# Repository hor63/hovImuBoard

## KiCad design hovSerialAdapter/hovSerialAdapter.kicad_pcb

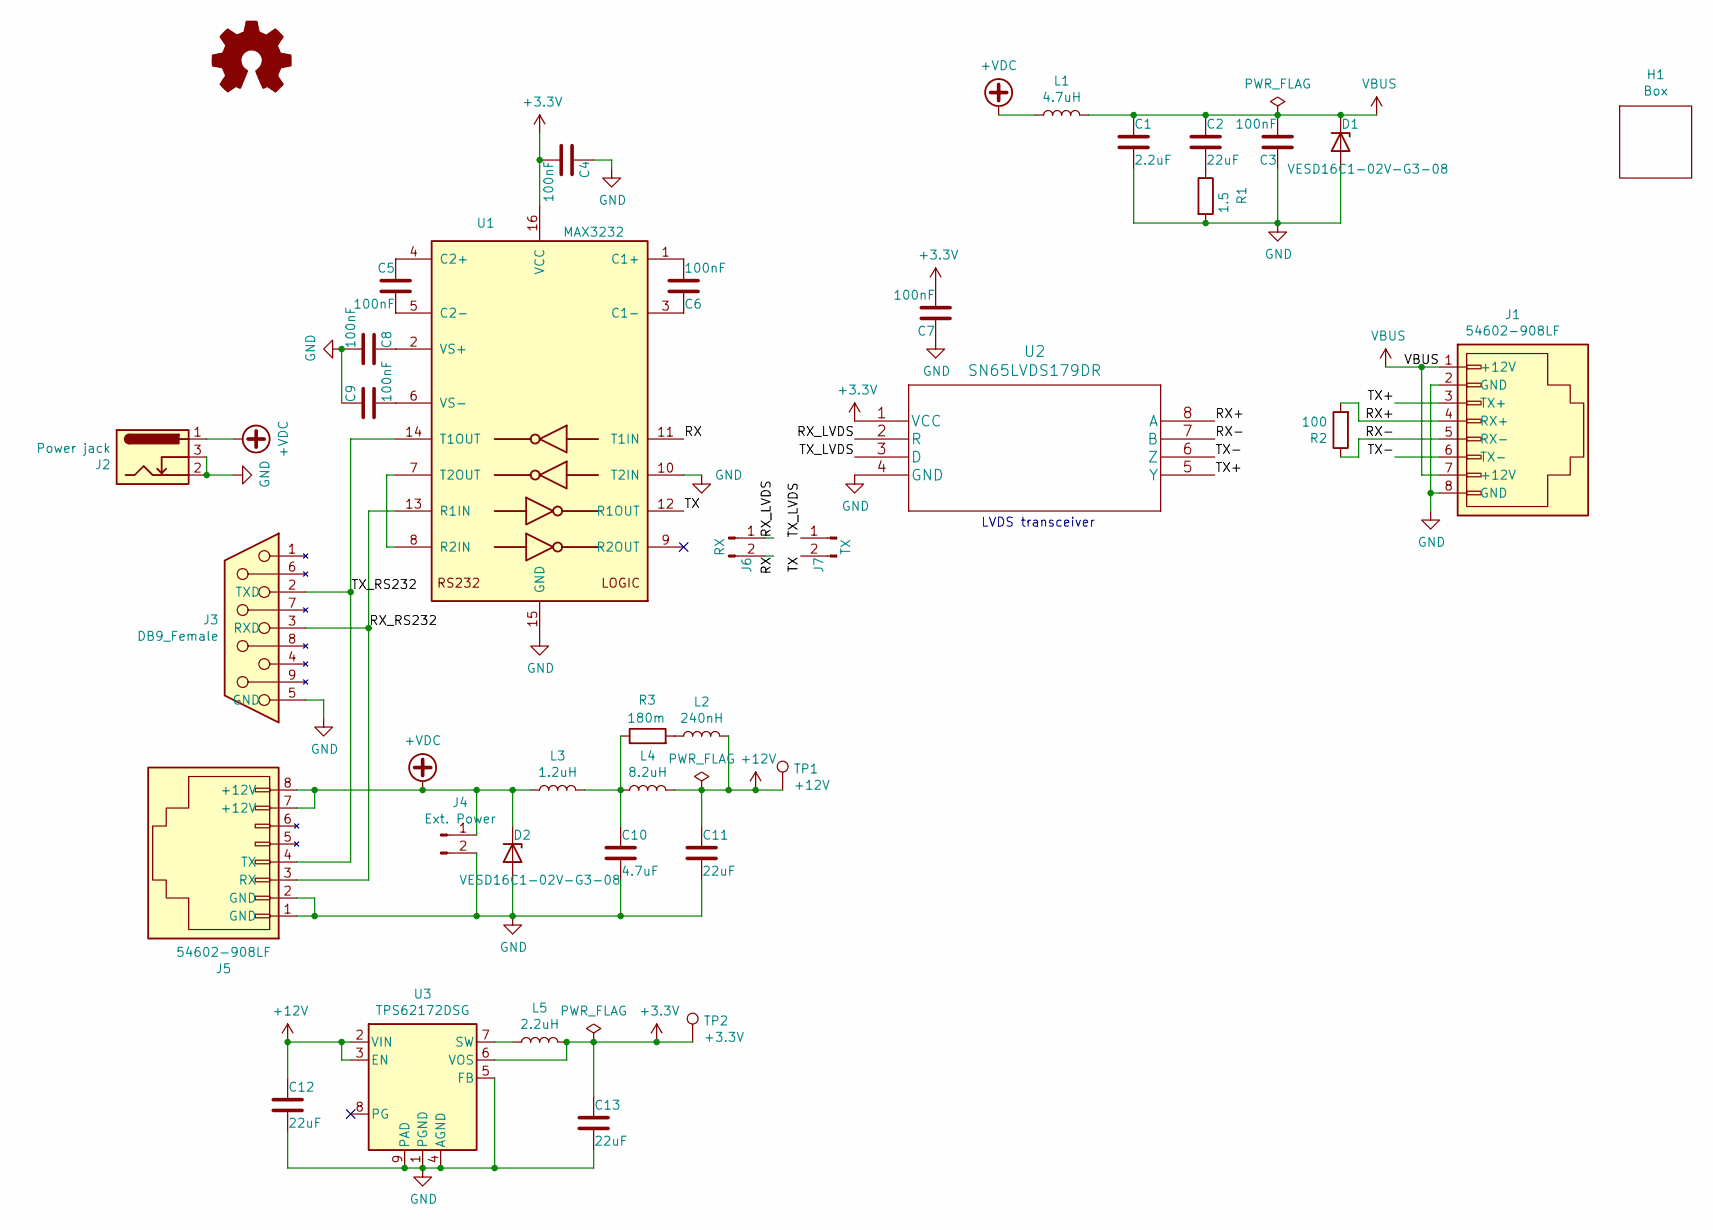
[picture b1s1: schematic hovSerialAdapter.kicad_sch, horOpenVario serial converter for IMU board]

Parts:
C1: 2.2uF; C_0805_2012Metric; MPN CL21B225KAFNNNE; Digi-Key_PN 1276-2954-1-ND
C2, C11, C12, C13: 22uF; C_1210_3225Metric; MPN CL32B226KAJNNNE; Digi-Key_PN 1276-3392-1-ND
C3, C4, C5, C6, C7, C8, C9: 100nF; C_0603_1608Metric; MPN CC0603KRX7R8BB104; Digi-Key_PN 311-1341-1-ND
C10: 4.7uF; C_1206_3216Metric; MPN C1206C475K3RACTU; Digi-Key_PN 399-8204-1-ND
D1, D2: VESD16C1-02V-G3-08; D_SOD-523; MPN VESD16C1-02V-G3-08; Digi-Key_PN VESD16C1-02V-G3-08GICT-ND
H1: Box; Box-MB655030; MPN MB655030; Digi-Key_PN HM5530-ND
J1, J5: 54602-908LF; Ethernet_Jack_54602-908LF; MPN 54602-908LF; Digi-Key_PN 609-1046-ND
J2: Power jack; CUI_PJ-036AH-SMT-TR; MPN PJ-036AH-SMT-TR; Digi-Key_PN CP-036AHPJCT-ND
J3: DB9_Female; DSUB-9_Female_EdgeMount_P2.77mm; MPN L77SDE09S; Digi-Key_PN L77SDE09S-ND
J4: Ext. Power; PinHeader_1x02_P2.54mm_Vertical
J6: RX; PinHeader_1x02_P2.54mm_Vertical
J7: TX; PinHeader_1x02_P2.54mm_Vertical
L1: 4.7uH; L_1812_4532Metric; MPN LQH43PN4R7M26L; Digi-Key_PN 490-13388-1-ND
L2: 240nH; L_0805_2012Metric; MPN LQM21PNR24MEHD; Digi-Key_PN 490-15988-1-ND
L3: 1.2uH; IND_1231AS-H-1R2N=P3; MPN 1231AS-H-1R2N=P3; Digi-Key_PN 490-14180-1-ND
L4: 8.2uH; IND_LQH43PH8R2M26L; MPN LQH43PH8R2M26L; Digi-Key_PN 490-16115-1-ND
L5: 2.2uH; IND_LQH3NPN2R2MMEL; MPN LQH3NPN2R2MMEL; Digi-Key_PN 490-15950-1-ND
LOGO1: Logo_Open_Hardware_Small; OSHW-Symbol_6.7x6mm_SilkScreen
R1: 1.5; R_0805_2012Metric; MPN ERJ-6DQF1R5V; Digi-Key_PN P19272CT-ND
R2: 100; R_0603_1608Metric; MPN ERJ-PA3F1000V; Digi-Key_PN P100BYCT-ND
R3: 180m; R_0805_2012Metric; MPN ERJ-6DSFR18V; Digi-Key_PN P19314CT-ND
TP1: +12V; TestPoint_THTPad_D1.0mm_Drill0.5mm
TP2: +3.3V; TestPoint_THTPad_D1.0mm_Drill0.5mm
U1: MAX3232; TSSOP-16_4.4x5mm_P0.65mm; MPN MAX3232IPWR; Digi-Key_PN 296-13100-1-ND
U2: SN65LVDS179DR; SOIC-8_3.9x4.9mm_P1.27mm; MPN SN65LVDS179DR; Digi-Key_PN 296-46329-1-ND
U3: TPS62172DSG; WSON-8-1EP_2x2mm_P0.5mm_EP0.9x1.6mm_ThermalVias; MPN TPS62172DSGR; Digi-Key_PN 296-39449-1-ND

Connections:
+3V3: C4.1, C7.1, C13.2, L5.2, TP2.1, U1.16 (VCC), U2.1 (VCC), U3.6 (VOS)
+12V: C11.2, C12.2, L2.2, L4.2, TP1.1, U3.2 (VIN), U3.3 (EN)
+VDC: D2.1 (K), J2.1, J4.1, J5.7 (+12V), J5.8 (+12V), L1.1, L3.1
/RX: J6.2, U1.11 (T1IN)
/RX+: J1.4 (RX+), R2.2, U2.8 (A)
/RX-: J1.5 (RX-), R2.1, U2.7 (B)
/RX_LVDS: J6.1, U2.2 (R)
/RX_RS232: J3.3 (RXD), J5.3 (RX), U1.13 (R1IN)
/TX: J7.2, U1.12 (R1OUT)
/TX+: J1.3 (TX+), U2.5 (Y)
/TX-: J1.6 (TX-), U2.6 (Z)
/TX_LVDS: J7.1, U2.3 (D)
/TX_RS232: J3.2 (TXD), J5.4 (TX), U1.14 (T1OUT)
GND: C1.1, C3.2, C4.2, C7.2, C8.1, C9.2, C10.1, C11.1, C12.1, C13.1, D1.2 (A), D2.2 (A), J1.2 (GND), J1.8 (GND), J2.2, J2.3, J3.5 (GND), J4.2, J5.1 (GND), J5.2 (GND), R1.2, U1.10 (T2IN), U1.15 (GND), U2.4 (GND), U3.1 (PGND), U3.4 (AGND), U3.5 (FB), U3.9 (PAD)
unnamed: C2.1, R1.1
unnamed: C5.1, U1.5 (C2-)
unnamed: C5.2, U1.4 (C2+)
unnamed: C6.1, U1.1 (C1+)
unnamed: C6.2, U1.3 (C1-)
unnamed: C8.2, U1.2 (VS+)
unnamed: C9.1, U1.6 (VS-)
unnamed: C10.2, L3.2, L4.1, R3.1
unnamed: L2.1, R3.2
unnamed: L5.1, U3.7 (SW)
unnamed: U1.7 (T2OUT), U1.8 (R2IN)
VBUS: C1.2, C2.2, C3.1, D1.1 (K), J1.1 (+12V), J1.7 (+12V), L1.2

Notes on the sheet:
LVDS transceiver

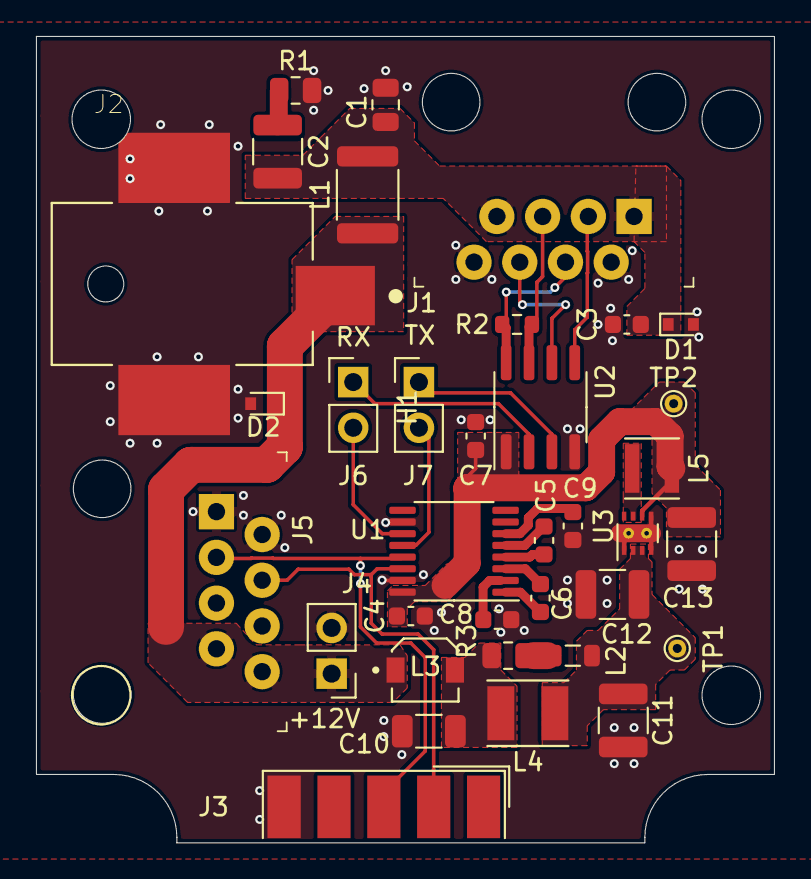
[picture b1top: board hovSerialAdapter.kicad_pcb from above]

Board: 2 copper layers, 41.0 x 44.8 mm, 37 parts (1 on the bottom side), 26 nets.

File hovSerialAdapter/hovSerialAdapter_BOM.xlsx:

Reference | Value | Description | Digi-Key_PN | MPN | Manufacturer | Qty
C1 | 2.2uF | CAP CER 2.2UF 25V X7R 0805 | 1276-2954-1-ND | CL21B225KAFNNNE | Samsung Electro-Mechanics | 1
> C3-C9 | 100nF | CAP CER 0.1UF 25V X7R 0603 | 311-1341-1-ND | CC0603KRX7R8BB104 | Yageo | 7
C10 | 4.7uF | CAP CER 4.7UF 25V X7R 1206 | 399-8204-1-ND | C1206C475K3RACTU | KEMET | 1
> C2, C11-C13 | 22uF | CAP CER 22UF 25V X7R 1210 | 1276-3392-1-ND | CL32B226KAJNNNE | Samsung Electro-Mechanics | 4
> D1, D2 | VESD16C1-02V-G3-08 | ESD PROTECTION DIODE 17V 6.3A SOD-523 | VESD16C1-02V-G3-08GICT-ND | VESD16C1-02V-G3-08 | Vishay Semiconductor Diodes Division | 2
H1 | Box | BOX PLASTIC GRAY 2.56"L X 1.97"W | HM5530-ND | MB655030 | Hammond Manufacturing | 1
J2 | Power jack | CONN PWR JACK 2X5.5MM SOLDER | CP-036AHPJCT-ND | PJ-036AH-SMT-TR | CUI Devices | 1
J3 | DB9_Female | CONN DSUB RCPT 9POS SLDR CUP | L77SDE09S-ND | L77SDE09S | Amphenol ICC (Commercial Products) | 1
J4 | Ext. Power | PinHeader1x02 P2.54mm Vertical |  |  |  | 1
> J1, J5 | 54602-908LF | CONN MOD JACK 8P8C R/A UNSHLD | 609-1046-ND | 54602-908LF | Amphenol ICC (FCI) | 2
J6 | RX | PinHeader1x02 P2.54mm Vertical |  |  |  | 1
J7 | TX | PinHeader1x02 P2.54mm Vertical |  |  |  | 1
L1 | 4.7uH | FIXED IND 4.7UH 1.6A 90 MOHM SMD | 490-13388-1-ND | LQH43PN4R7M26L | Murata Electronics | 1
L2 | 240nH | FIXED IND 240NH 2.4A 50 MOHM | 490-15988-1-ND | LQM21PNR24MEHD | Murata Electronics | 1
L3 | 1.2uH | FIXED IND 1.2UH 2.9A 36 MOHM | 490-14180-1-ND | 1231AS-H-1R2N=P3 | Murata Electronics | 1
L4 | 8.2uH | FIXED IND 8.2UH 1.3A 153.6 MOHM | 490-16115-1-ND | LQH43PH8R2M26L | Murata Electronics | 1
L5 | 2.2uH | FIXED IND 2.2UH 2.1A 78 MOHM | 490-15950-1-ND | LQH3NPN2R2MMEL | Murata Electronics | 1
LOGO1 | Logo_Open_Hardware_Small |  |  |  |  | 1
R1 | 1.5 | RES SMD 1.5 OHM 1% 1/2W 0805 | P19272CT-ND | ERJ-6DQF1R5V | Panasonic Electronic Components | 1
R2 | 100 | RES SMD 100 OHM 1% 1/4W 0603 | P100BYCT-ND | ERJ-PA3F1000V | Panasonic Electronic Components | 1
R3 | 180m | RES 0.18 OHM 1% 1/2W 0805 | P19314CT-ND | ERJ-6DSFR18V | Panasonic Electronic Components | 1
TP1 | +12V |  |  |  |  | 1
TP2 | +3.3V |  |  |  |  | 1
U1 | MAX3232 | IC TRANSCEIVER FULL 2/2 16TSSOP | 296-13100-1-ND | MAX3232IPWR | Texas Instruments | 1
U2 | SN65LVDS179DR | LVDS TRANSCEIVER FULL 1/1 8SOIC | 296-46329-1-ND | SN65LVDS179DR | Texas Instruments | 1
U3 | TPS62172DSG | IC REG BUCK 3.3V 500MA 8WSON | 296-39449-1-ND | TPS62172DSGR | Texas Instruments | 1

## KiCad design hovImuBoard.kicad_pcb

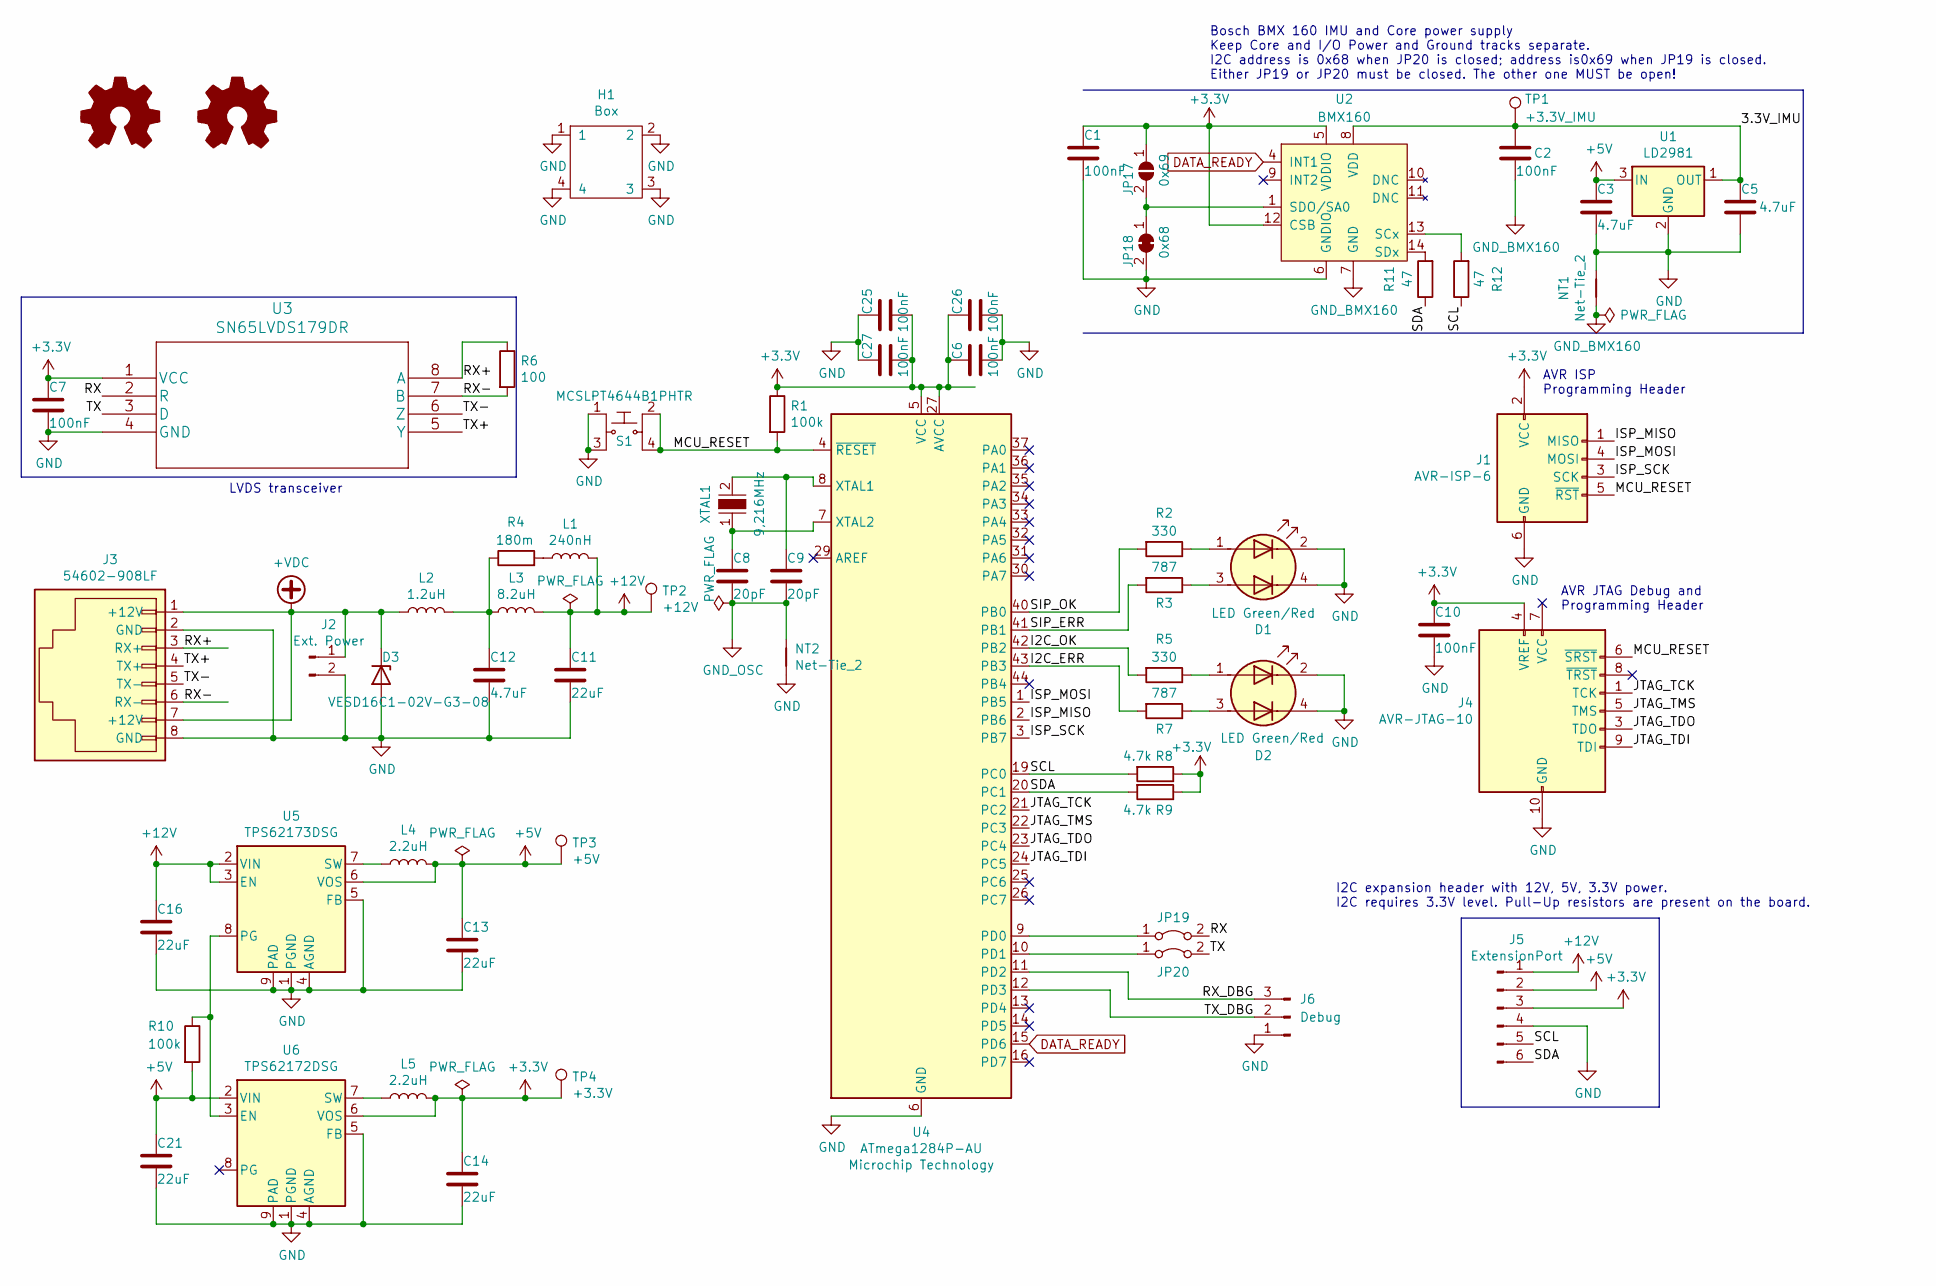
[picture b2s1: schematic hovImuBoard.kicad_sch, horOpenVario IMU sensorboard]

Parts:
C1, C2: 100nF; C_0603_1608Metric; MPN 060330160104JXT; Digi-Key_PN 1608-1295-1-ND
C3, C5, C12: 4.7uF; C_1206_3216Metric; MPN C1206C475K3RACTU; Digi-Key_PN 399-8204-1-ND
C6, C7, C10, C25, C26, C27: 100nF; C_0603_1608Metric; MPN CC0603KRX7R8BB104; Digi-Key_PN 311-1341-1-ND
C8, C9: 20pF; C_0603_1608Metric; MPN CC0603JRNPO9BN200; Digi-Key_PN 311-1424-1-ND
C11, C13, C14, C16, C21: 22uF; C_1210_3225Metric; MPN CL32B226KAJNNNE; Digi-Key_PN 1276-3392-1-ND
D1, D2: LED Green/Red; LED_APHB1608LZGKSURKC; MPN APHB1608LZGKSURKC; Digi-Key_PN 754-1955-1-ND
D3: VESD16C1-02V-G3-08; D_SOD-523; MPN VESD16C1-02V-G3-08; Digi-Key_PN VESD16C1-02V-G3-08GICT-ND
H1: Box; Box-CU-1935-MB; MPN CU-1935-MB; Digi-Key_PN 377-1757-ND
J1: AVR-ISP-6; TE_1761681-1; MPN 1761681-1; Digi-Key_PN A122759-ND
J2: Ext. Power; PinHeader_1x02_P2.54mm_Vertical
J3: 54602-908LF; Ethernet_Jack_54602-908LF; MPN 54602-908LF; Digi-Key_PN 609-1046-ND
J4: AVR-JTAG-10; PinHeader_2x5_P1.27mm_Drill.7mm; MPN SHF-105-01-L-D-TH; Digi-Key_PN SAM10711-ND
J5: ExtensionPort; PinHeader_1x06_P2.54mm_Vertical
J6: Debug; PinHeader_1x03_P2.54mm_Vertical
JP17: 0x69; SolderJumper-2_P1.3mm_Open_RoundedPad1.0x1.5mm
JP18: 0x68; SolderJumper-2_P1.3mm_Bridged_RoundedPad1.0x1.5mm
JP19, JP20: Jumper_2_Bridged; PinHeader_1x02_P2.54mm_Vertical
L1: 240nH; L_0805_2012Metric; MPN LQM21PNR24MEHD; Digi-Key_PN 490-15988-1-ND
L2: 1.2uH; IND_1231AS-H-1R2N=P3; MPN 1231AS-H-1R2N=P3; Digi-Key_PN 490-14180-1-ND
L3: 8.2uH; L_1812_4532Metric; MPN LQH43PN8R2M26L; Digi-Key_PN 490-16860-1-ND
L4, L5: 2.2uH; IND_LQH3NPN2R2MMEL; MPN LQH3NPN2R2MMEL; Digi-Key_PN 490-15950-1-ND
LOGO1, LOGO2: Logo_Open_Hardware_Small; OSHW-Symbol_6.7x6mm_Copper
NT1: Net-Tie_2; NetTie-2_SMD_Pad2.0mm
NT2: Net-Tie_2; NetTie-2_SMD_Pad0.5mm
R1: 100k; R_0805_2012Metric; MPN CRCW0805100KFKEA; Digi-Key_PN 541-100KCCT-ND
R2, R5: 330; R_0603_1608Metric; MPN ERJ-3EKF3300V; Digi-Key_PN P330HCT-ND
R3, R7: 787; R_0603_1608Metric; MPN ERJ-3EKF7870V; Digi-Key_PN P787HCT-ND
R4: 180m; R_0805_2012Metric; MPN ERJ-6DSFR18V; Digi-Key_PN P19314CT-ND
R6: 100; R_0603_1608Metric; MPN ERJ-PA3F1000V; Digi-Key_PN P100BYCT-ND
R8, R9: 4.7k; R_0603_1608Metric; MPN ERJ-3EKF4701V; Digi-Key_PN P4.70KHCT-ND
R10: 100k; R_0603_1608Metric; MPN ERJ-3EKF1003V; Digi-Key_PN P100KHCT-ND
R11, R12: 47; R_0603_1608Metric; MPN ERJ-3EKF47R0V; Digi-Key_PN P47.0HCT-ND
S1: MCSLPT4644B1PHTR; PB_MCSLPT4644B1PHTR; MPN MCSLPT4644B1PHTR; Digi-Key_PN 450-3383-1-ND
TP1: +3.3V_IMU; TestPoint_THTPad_D1.0mm_Drill0.5mm
TP2: +12V; TestPoint_THTPad_D1.0mm_Drill0.5mm
TP3: +5V; TestPoint_THTPad_D1.0mm_Drill0.5mm
TP4: +3.3V; TestPoint_THTPad_D1.0mm_Drill0.5mm
U1: LD2981; SOT-89-3; MPN LD2981ABU33TR; Digi-Key_PN 497-1524-1-ND
U2: BMX160; Bosch_LGA-14_3x2.5mm_P0.5mm; MPN BMX160; Digi-Key_PN 828-1087-1-ND
U3: SN65LVDS179DR; SOIC-8_3.9x4.9mm_P1.27mm; MPN SN65LVDS179DR; Digi-Key_PN 296-46329-1-ND
U4: ATmega1284P-AU; TQFP-44_10x10mm_P0.8mm; MPN ATmega1284P-AU; Digi-Key_PN ATmega1284P-AU-ND
U5: TPS62173DSG; WSON-8-1EP_2x2mm_P0.5mm_EP0.9x1.6mm_ThermalVias; MPN TPS62173DSGR; Digi-Key_PN 296-39450-1-ND
U6: TPS62172DSG; WSON-8-1EP_2x2mm_P0.5mm_EP0.9x1.6mm_ThermalVias; MPN TPS62172DSGR; Digi-Key_PN 296-39449-1-ND
XTAL1: 9,216MHz; Crystal_SMD_HC49-SD; MPN ECS-92.1-20-5PX-TR; Digi-Key_PN XC1274CT-ND

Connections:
+3V3: C1.2, C6.2, C7.2, C10.2, C14.2, C25.1, C26.2, C27.1, J1.2 (VCC), J4.4 (VREF), J5.3, JP17.1 (A), L5.2, R1.1, R8.1, R9.1, TP4.1, U2.5 (VDDIO), U2.12 (CSB), U3.1 (VCC), U4.5 (VCC), U4.17 (VCC), U4.27 (AVCC), U4.38 (VCC), U6.6 (VOS)
+5V: C3.2, C13.2, C21.2, J5.2, L4.2, R10.2, TP3.1, U1.3 (IN), U5.6 (VOS), U6.2 (VIN)
+12V: C11.2, C16.2, J5.1, L1.2, L3.2, TP2.1, U5.2 (VIN), U5.3 (EN)
+VDC: D3.1 (K), J2.1, J3.1 (+12V), J3.7 (+12V), L2.1
/3.3V_IMU: C2.2, C5.2, TP1.1, U1.1 (OUT), U2.8 (VDD)
/DATA_READY: U2.4 (INT1), U4.15 (PD6)
/I2C_ERR: R7.2, U4.43 (PB3)
/I2C_OK: R5.2, U4.42 (PB2)
/ISP_MISO: J1.1 (MISO), U4.2 (PB6)
/ISP_MOSI: J1.4 (MOSI), U4.1 (PB5)
/ISP_SCK: J1.3 (SCK), U4.3 (PB7)
/JTAG_TCK: J4.1 (TCK), U4.21 (PC2)
/JTAG_TDI: J4.9 (TDI), U4.24 (PC5)
/JTAG_TDO: J4.3 (TDO), U4.23 (PC4)
/JTAG_TMS: J4.5 (TMS), U4.22 (PC3)
/MCU_RESET: J1.5 (~RST), J4.6 (~SRST), R1.2, S1.2, S1.4, U4.4 (~RESET)
/RX: JP19.2 (B), U3.2 (R)
/RX+: J3.3 (RX+), R6.1, U3.8 (A)
/RX-: J3.6 (RX-), R6.2, U3.7 (B)
/RX_DBG: J6.3, U4.11 (PD2)
/SCL: J5.5, R8.2, R12.1, U4.19 (PC0)
/SDA: J5.6, R9.2, R11.1, U4.20 (PC1)
/SIP_ERR: R3.2, U4.41 (PB1)
/SIP_OK: R2.2, U4.40 (PB0)
/TX: JP20.2 (B), U3.3 (D)
/TX+: J3.4 (TX+), U3.5 (Y)
/TX-: J3.5 (TX-), U3.6 (Z)
/TX_DBG: J6.2, U4.12 (PD3)
GND: C1.1, C3.1, C5.1, C6.1, C7.1, C10.1, C11.1, C12.1, C13.1, C14.1, C16.1, C21.1, C25.2, C26.1, C27.2, D1.2 (K1), D1.4 (K2), D2.2 (K1), D2.4 (K2), D3.2 (A), H1.1, H1.2, H1.3, H1.4, J1.6 (GND), J2.2, J3.2 (GND), J3.8 (GND), J4.2 (GND), J4.10 (GND), J5.4, J6.1, JP18.2 (B), NT1.2, NT2.2, S1.1, S1.3, U1.2 (GND), U2.6 (GNDIO), U3.4 (GND), U4.6 (GND), U4.18 (GND), U4.28 (GND), U4.39 (GND), U5.1 (PGND), U5.4 (AGND), U5.5 (FB), U5.9 (PAD), U6.1 (PGND), U6.4 (AGND), U6.5 (FB), U6.9 (PAD)
GND_BMX160: C2.1, NT1.1, U2.2 (GND), U2.3 (GND), U2.7 (GND)
GND_OSC: C8.1, C9.1, NT2.1
unnamed: C8.2, U4.7 (XTAL2), XTAL1.1
unnamed: C9.2, U4.8 (XTAL1), XTAL1.2
unnamed: C12.2, L2.2, L3.1, R4.1
unnamed: D1.1 (A1), R2.1
unnamed: D1.3 (A2), R3.1
unnamed: D2.1 (A1), R5.1
unnamed: D2.3 (A2), R7.1
unnamed: JP17.2 (B), JP18.1 (A), U2.1 (SDO/SA0)
unnamed: JP19.1 (A), U4.9 (PD0)
unnamed: JP20.1 (A), U4.10 (PD1)
unnamed: L1.1, R4.2
unnamed: L4.1, U5.7 (SW)
unnamed: L5.1, U6.7 (SW)
unnamed: R10.1, U5.8 (PG), U6.3 (EN)
unnamed: R11.2, U2.14 (SDx)
unnamed: R12.2, U2.13 (SCx)

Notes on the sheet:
I2C expansion header with 12V, 5V, 3.3V power. I2C requires 3.3V level. Pull-Up resistors are present on the board.
AVR JTAG Debug and Programming Header
LVDS transceiver
AVR ISP Programming Header
Bosch BMX 160 IMU and Core power supply Keep Core and I/O Power and Ground tracks separate. I2C address is 0x68 when JP20 is closed; address is0x69 when JP19 is closed. Either JP19 or JP20 must be closed. The other one MUST be open!

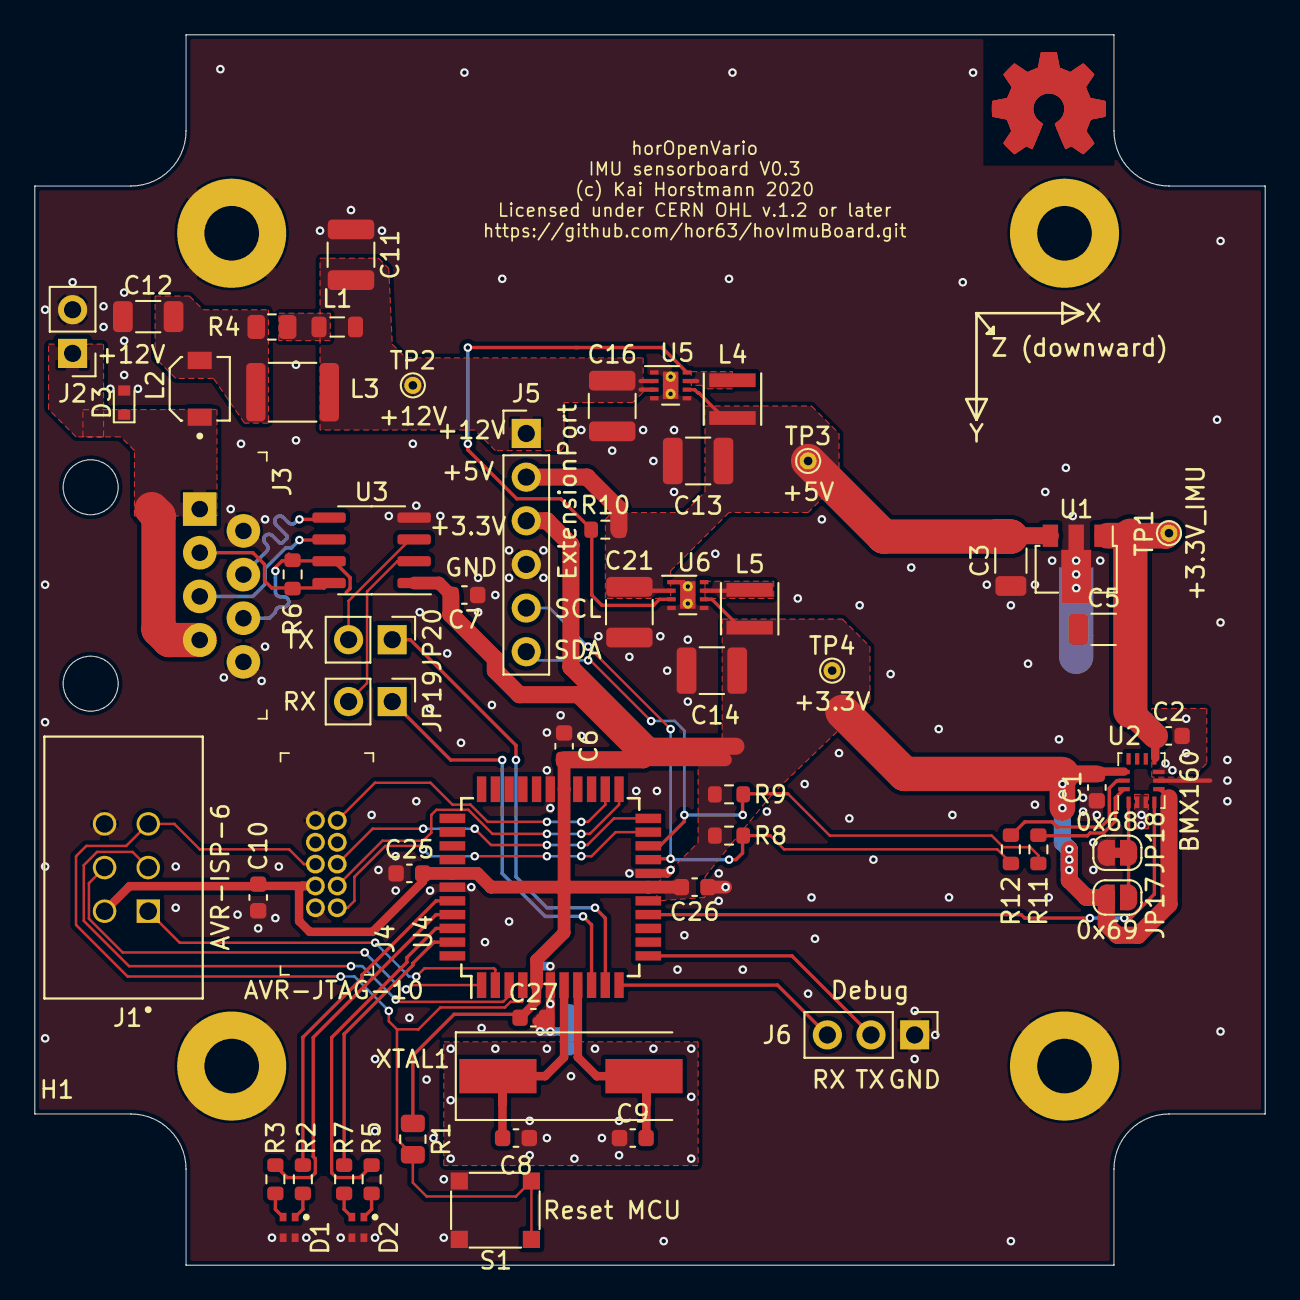
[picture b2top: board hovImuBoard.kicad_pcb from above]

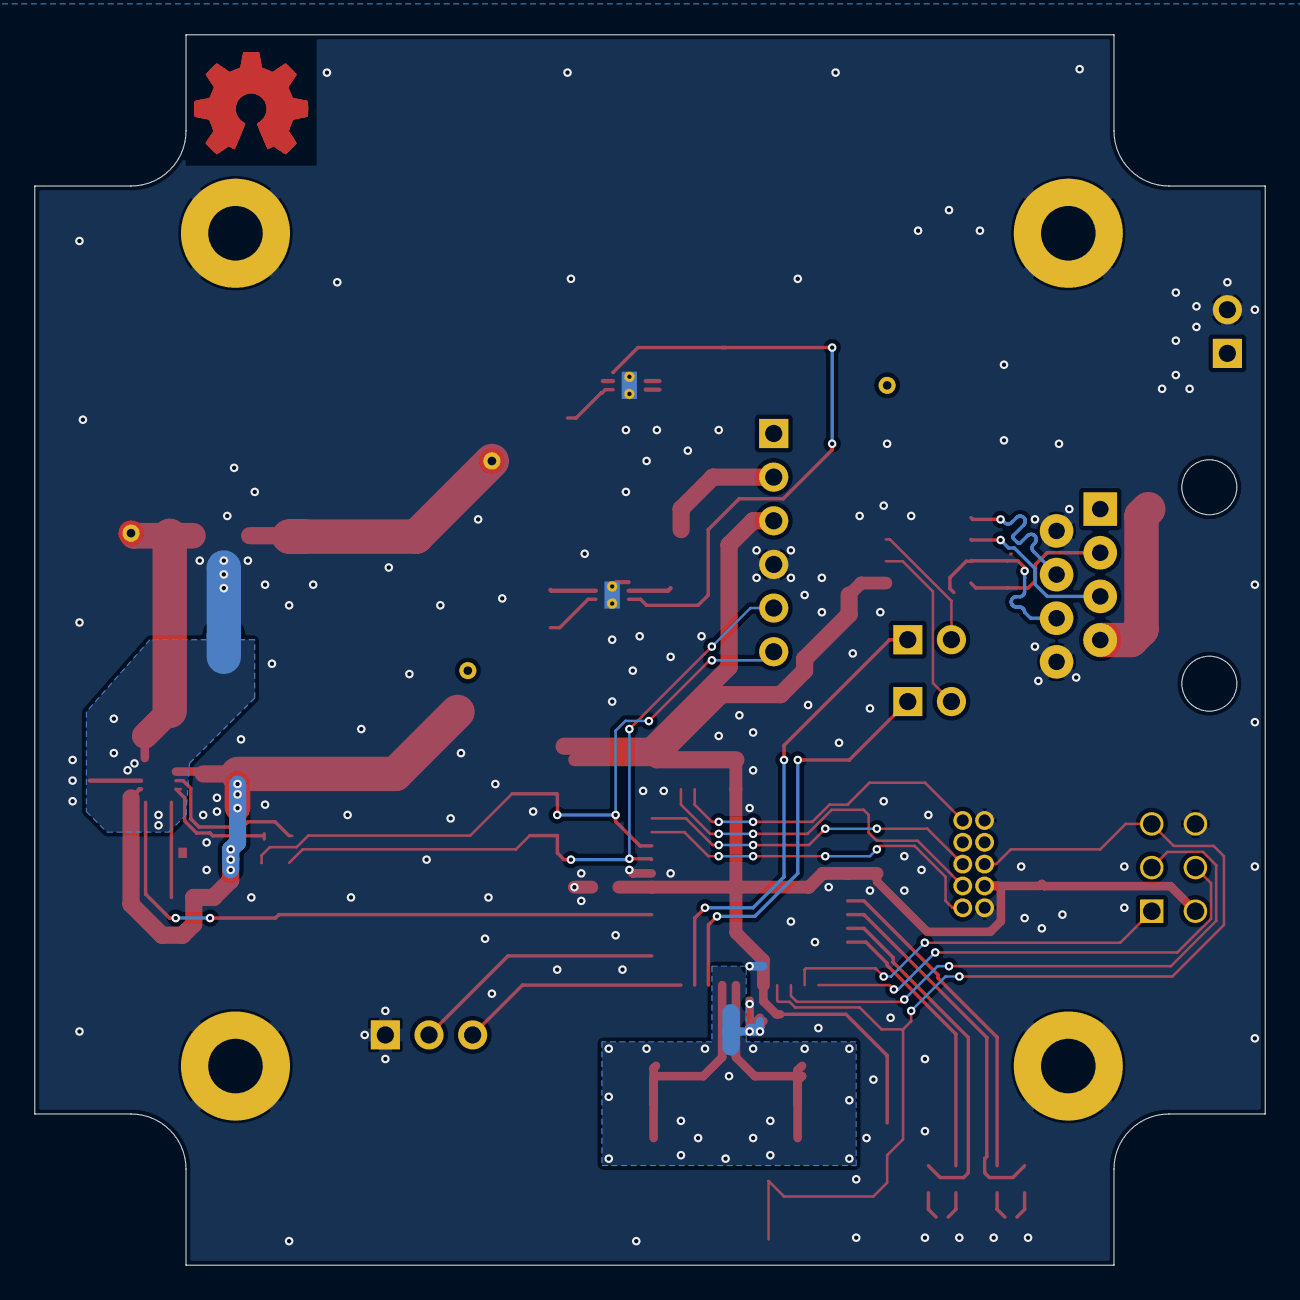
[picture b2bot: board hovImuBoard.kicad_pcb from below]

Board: 2 copper layers, 71.6 x 71.6 mm, 65 parts (2 on the bottom side), 47 nets.

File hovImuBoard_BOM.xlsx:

Reference | Value | Description | Digi-Key_PN | MPN | Manufacturer | Qty
> C1, C2 | 100nF | CAP CER 0.1UF 25V X7R 0603 Non-magnetic | 1608-1295-1-ND | 060330160104JXT | Knowles Syfer | 2
> C6, C7, C10, C25-C27 | 100nF | CAP CER 0.1UF 25V X7R 0603 | 311-1341-1-ND | CC0603KRX7R8BB104 | Yageo | 6
> C8, C9 | 20pF | CAP CER 20PF 50V C0G/NPO 0603 | 311-1424-1-ND | CC0603JRNPO9BN200 | Yageo | 2
> C3, C5, C12 | 4.7uF | CAP CER 4.7UF 25V X7R 1206 | 399-8204-1-ND | C1206C475K3RACTU | KEMET | 3
> C11, C13, C14, C16, C21 | 22uF | CAP CER 22UF 25V X7R 1210 | 1276-3392-1-ND | CL32B226KAJNNNE | Samsung Electro-Mechanics | 5
> D1, D2 | LED Green/Red | LED GREEN/RED CLEAR 4SMD | 754-1955-1-ND | APHB1608LZGKSURKC | Kingbright | 2
D3 | VESD16C1-02V-G3-08 | ESD PROTECTION DIODE 17V 6.3A SOD-523 | VESD16C1-02V-G3-08GICT-ND | VESD16C1-02V-G3-08 | Vishay Semiconductor Diodes Division | 1
H1 | Box |  | 377-1757-ND | CU-1935-MB | Bud Industries | 1
J1 | AVR-ISP-6 | TE_1761681-1 | A122759-ND | 1761681-1 | TE Connectivity AMP Connectors | 1
J3 | 54602-908LF | CONN MOD JACK 8P8C R/A UNSHLD | 609-1046-ND | 54602-908LF | Amphenol ICC (FCI) | 1
J4 | AVR-JTAG-10 | SHF-105-01-L-D-TH | SAM10711-ND | SHF-105-01-L-D-TH | Samtec Inc. | 1
L1 | 240nH | FIXED IND 240NH 2.4A 50 MOHM | 490-15988-1-ND | LQM21PNR24MEHD | Murata Electronics | 1
L2 | 1.2uH | FIXED IND 1.2UH 2.9A 36 MOHM | 490-14180-1-ND | 1231AS-H-1R2N=P3 | Murata Electronics | 1
L3 | 8.2uH | FIXED IND 8.2UH 1.3A 128 MOHM | 490-16860-1-ND | LQH43PN8R2M26L | Murata Electronics | 1
> L4, L5 | 2.2uH | FIXED IND 2.2UH 2.1A 78 MOHM | 490-15950-1-ND | LQH3NPN2R2MMEL | Murata Electronics | 2
R1 | 100k |  | 541-100KCCT-ND | CRCW0805100KFKEA | Vishay Dale | 1
> R2, R5 | 330 | RES SMD 330 OHM 1% 1/10W 0603 | P330HCT-ND | ERJ-3EKF3300V | Panasonic Electronic Components | 2
> R3, R7 | 787 | RES SMD 787 OHM 1% 1/10W 0603 | P787HCT-ND | ERJ-3EKF7870V | Panasonic Electronic Components | 2
R4 | 180m | RES 0.18 OHM 1% 1/2W 0805 | P19314CT-ND | ERJ-6DSFR18V | Panasonic Electronic Components | 1
R6 | 100 | RES SMD 100 OHM 1% 1/4W 0603 | P100BYCT-ND | ERJ-PA3F1000V | Panasonic Electronic Components | 1
> R8, R9 | 4.7k | RES SMD 4.7K OHM 1% 1/10W 0603 | P4.70KHCT-ND | ERJ-3EKF4701V | Panasonic Electronic Components | 2
R10 | 100k | RES SMD 100K OHM 1% 1/10W 0603 | P100KHCT-ND | ERJ-3EKF1003V | Panasonic Electronic Components | 1
> R11, R12 | 47 | RES SMD 47 OHM 1% 1/10W 0603 | P47.0HCT-ND | ERJ-3EKF47R0V | Panasonic Electronic Components | 2
S1 | MCSLPT4644B1PHTR |  | 450-3383-1-ND | MCSLPT4644B1PHTR | TE Connectivity ALCOSWITCH Switches | 1
U1 | LD2981 |  | 497-1524-1-ND | LD2981ABU33TR | STMicroelectronics | 1
U2 | BMX160 | Accelerometer, Gyroscope, Magnetometer, 3 Axis Sensor I²C, SPI Output | 828-1087-1-ND | BMX160 | Bosch Sensortec | 1
U3 | SN65LVDS179DR | LVDS TRANSCEIVER FULL 1/1 8SOIC | 296-46329-1-ND | SN65LVDS179DR | Texas Instruments | 1
U4 | ATmega1284P-AU | IC MCU 8BIT 128KB FLASH 44TQFP | ATmega1284P-AU-ND | ATmega1284P-AU | Microchip Technology | 1
U5 | TPS62173DSG | IC REG BUCK 5V 500MA 8WSON | 296-39450-1-ND | TPS62173DSGR | Texas Instruments | 1
U6 | TPS62172DSG | IC REG BUCK 3.3V 500MA 8WSON | 296-39449-1-ND | TPS62172DSGR | Texas Instruments | 1
XTAL1 | 9,216MHz | CRYSTAL 9.2160MHZ 20PF SMD | XC1274CT-ND | ECS-92.1-20-5PX-TR | ECS Inc. | 1

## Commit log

2019-08-19 Initial checkin of WIP
2019-08-20 First shot routing the board
    Simplified the design: The IP address is not configurable with solder jumpers any more.
2019-08-22 Re-arrange expansion port and LEDs. Route power further apart from the BMX160 Add mounting holes.
2019-09-06 Apply corrections from V0.1; Fit board to a plastic box
2019-09-06 Correct L4 and L5 to 2.2uH. Update BOM
2019-09-20 Remove superfluous fields from symbols like Digi-Key data sheets, or family
2019-09-20 Update BOM
2019-09-20 Optimize the layout.
    Re-route tracks inside the screw hole.
    Remove some vias connecting the ground planes.
    Re-route tracks inside the ATMega to allow better connection between ground planes.
    Overlay ground copper zones to add thermal relief to manually soldered items.
2019-10-06 Update ATMega1284P datasheet link, add datasheets of active parts.
2019-10-25 Add BMI160 and BMM150 datasheets. BMX160 is a combination of the former two. The datasheets contain more details, particularly the BMM15 datasheet in regards to the data representation of MAG and RHa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
2020-07-09 WIP: Redesign of the sensor board.
    Major re-design:
    - LVDS instead of RS422 driver
    - Simplify buck converter design.
    - Make the back-plane mostly un-interrupted.
    - Smaller cpacitors, eliminate tantal capacitors.
    - Make ESD diode smaller.
2020-07-10 Complete re-design of hovImuBoard
    - Create a proper local ground plane for the oscillator
    - Create a local ground plane for the analog and digital ground.
    - Clean separation of VDD and VDDIO, and ground lines for I/O.
    - Hook up INT1 of the IMU with pin 15 of the MCU
2020-07-15 Rev. is 0.3, minor trace optimiztions.
2020-07-15 Add directory hovSerialAdapter
    Add new PCB as converter from RS-232 or TTL level to LVDS to the
    IMU board.
    The serial converter board also provides filtered power to the IMU board.
    Un-filtered power can come either from a IGC compatible RJ-45 jack, a 2mm/5mm barrel jack
    or just pin headers.
    Add reference to project symbol tables
2020-07-26 Finalize design of serial adapter board V0.1
    Add box symbol and footprint.
    Finishing touches on the routings
2020-07-26 Remove one power symbol
2020-08-05 hovSerialAdapter: Add 3D models from SnapEDA.
    Add 3D models from SnapEDA to the footprints of the RJ-45 jack, and for the 8.2uH inductivity
2020-08-07 hovSerialAdapter: Add 3D model for the D-Sub connector.
    Copy the footprint to lib/hovImuBoard.pretty, and add the 3D model.
    Improve the switching trace on the 3.3V regulator, moving the feedback further out of the way
2021-06-24 Doc: Add LVDS driver sn65lvds179 datasheet
2021-06-24 Serial adapter: Update BOM
2021-06-24 Update KiCad, and libraries
2022-01-31 Conversion to KiCad 6.0, add 3D models
    First commit after successful conversion.
    Save first before cleanup of outdated KiCad 5 files. Just to be sure.
    Added missing 3D models for various parts. Downloaded from SNAP-EDA or
    directly from the manufacturer's site.
2022-05-13 Doc: Add u-Blox 6 module datasheet and long-distance setup for UBlox module.
    The long-distance setup uses the IMU board and the serial converter board to
    bridge longer distance (i.e. from my desk out to the patio) with a long
    Ethernet patch cable using the LVDS data and power connection between the two
    boards.
2022-05-16 Latest update for SPICE simulation

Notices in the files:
hovImuBoard.kicad_pcb:
Licensed under CERN OHL v.1.2 or later
